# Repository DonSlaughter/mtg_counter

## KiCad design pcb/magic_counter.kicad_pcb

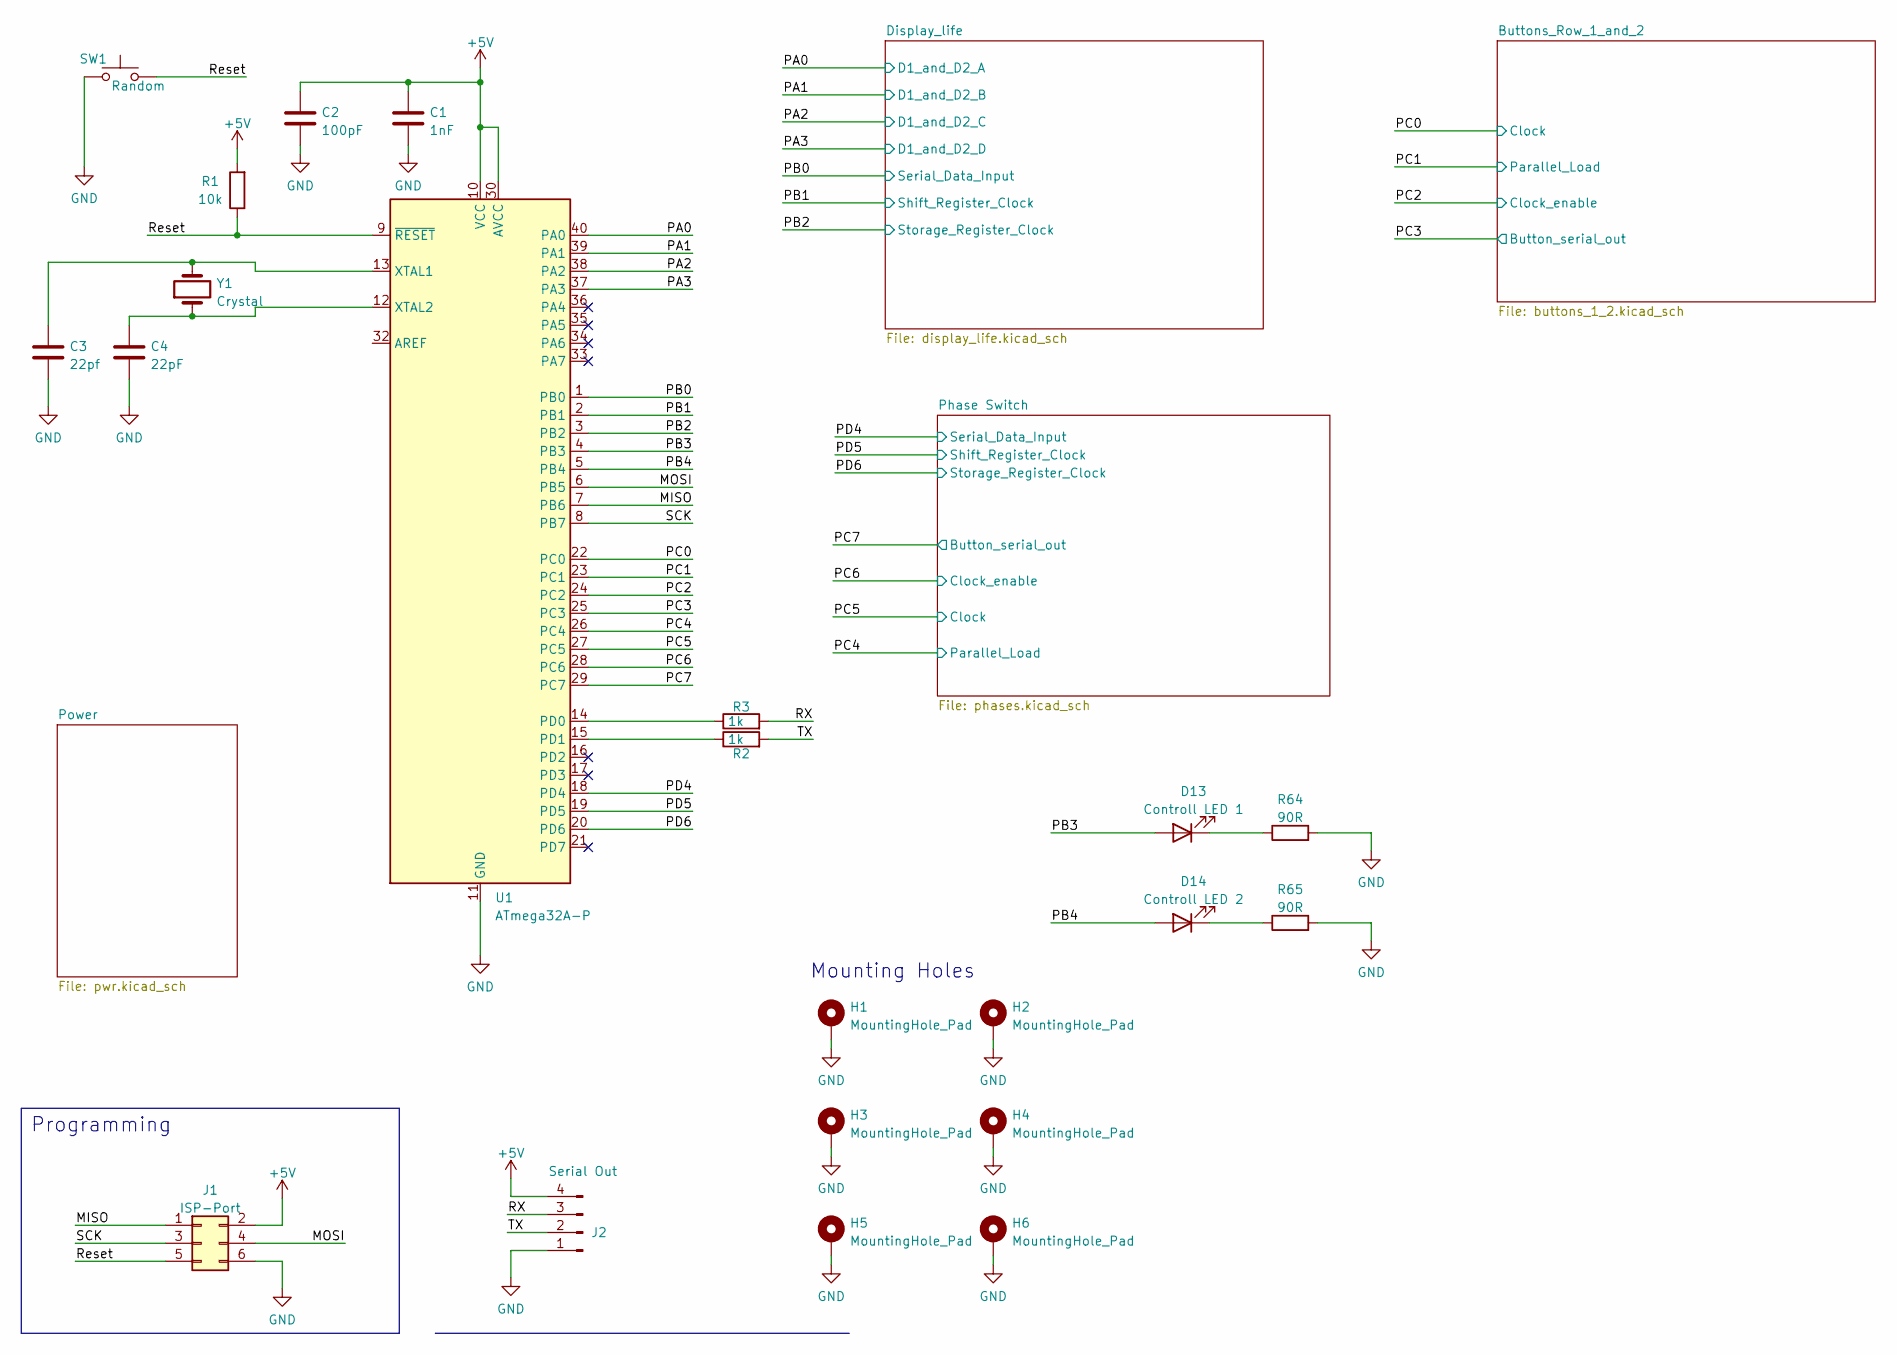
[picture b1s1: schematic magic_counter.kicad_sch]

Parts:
C1: 1nF; C_Disc_D3.8mm_W2.6mm_P2.50mm
C2: 100pF; C_Disc_D3.8mm_W2.6mm_P2.50mm
C3: 22pf; C_Disc_D3.8mm_W2.6mm_P2.50mm
C4: 22pF; C_Disc_D3.8mm_W2.6mm_P2.50mm
D13: Controll LED 1; LED_D5.0mm
D14: Controll LED 2; LED_D5.0mm
H1, H2, H3, H4, H5, H6: MountingHole_Pad; MountingHole_3.2mm_M3_DIN965_Pad
J1: ISP-Port; IDC-Header_2x03_P2.54mm_Vertical
J2: Serial Out; PinHeader_1x04_P2.54mm_Vertical
R1: 10k; R_Axial_DIN0207_L6.3mm_D2.5mm_P7.62mm_Horizontal
R2, R3: 1k; R_Axial_DIN0207_L6.3mm_D2.5mm_P7.62mm_Horizontal
R64, R65: 90R; R_Axial_DIN0207_L6.3mm_D2.5mm_P7.62mm_Horizontal
SW1: Random; SW_PUSH_6mm_H5mm
U1: ATmega32A-P; DIP-40_W15.24mm_LongPads
Y1: Crystal; Crystal_HC49-4H_Vertical

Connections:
+5V: C1.1, C2.1, J1.2, J2.4, R1.2, U1.10 (VCC), U1.30 (AVCC); also elsewhere on the board
/MISO: J1.1, U1.7 (PB6)
/MOSI: J1.4, U1.6 (PB5)
/PA0: U1.40 (PA0); also elsewhere on the board
/PA1: U1.39 (PA1); also elsewhere on the board
/PA2: U1.38 (PA2); also elsewhere on the board
/PA3: U1.37 (PA3); also elsewhere on the board
/PB0: U1.1 (PB0); also elsewhere on the board
/PB1: U1.2 (PB1); also elsewhere on the board
/PB2: U1.3 (PB2); also elsewhere on the board
/PB3: D13.2 (A), U1.4 (PB3)
/PB4: D14.2 (A), U1.5 (PB4)
/PC0: U1.22 (PC0); also elsewhere on the board
/PC1: U1.23 (PC1); also elsewhere on the board
/PC2: U1.24 (PC2); also elsewhere on the board
/PC3: U1.25 (PC3); also elsewhere on the board
/PC4: U1.26 (PC4); also elsewhere on the board
/PC5: U1.27 (PC5); also elsewhere on the board
/PC6: U1.28 (PC6); also elsewhere on the board
/PC7: U1.29 (PC7); also elsewhere on the board
/PD4: U1.18 (PD4); also elsewhere on the board
/PD5: U1.19 (PD5); also elsewhere on the board
/PD6: U1.20 (PD6); also elsewhere on the board
/RX: J2.3, R3.2
/Reset: J1.5, R1.1, SW1.2, U1.9 (~RESET)
/SCK: J1.3, U1.8 (PB7)
/TX: J2.2, R2.2
GND: C1.2, C2.2, C3.2, C4.2, H1.1, H2.1, H3.1, H4.1, H5.1, H6.1, J1.6, J2.1, R64.2, R65.2, SW1.1, U1.11 (GND), U1.31 (GND); also elsewhere on the board
unnamed: C3.1, U1.13 (XTAL1), Y1.2
unnamed: C4.1, U1.12 (XTAL2), Y1.1
unnamed: D13.1 (K), R64.1
unnamed: D14.1 (K), R65.1
unnamed: R2.1, U1.15 (PD1)
unnamed: R3.1, U1.14 (PD0)

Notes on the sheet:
Mounting Holes
Programming

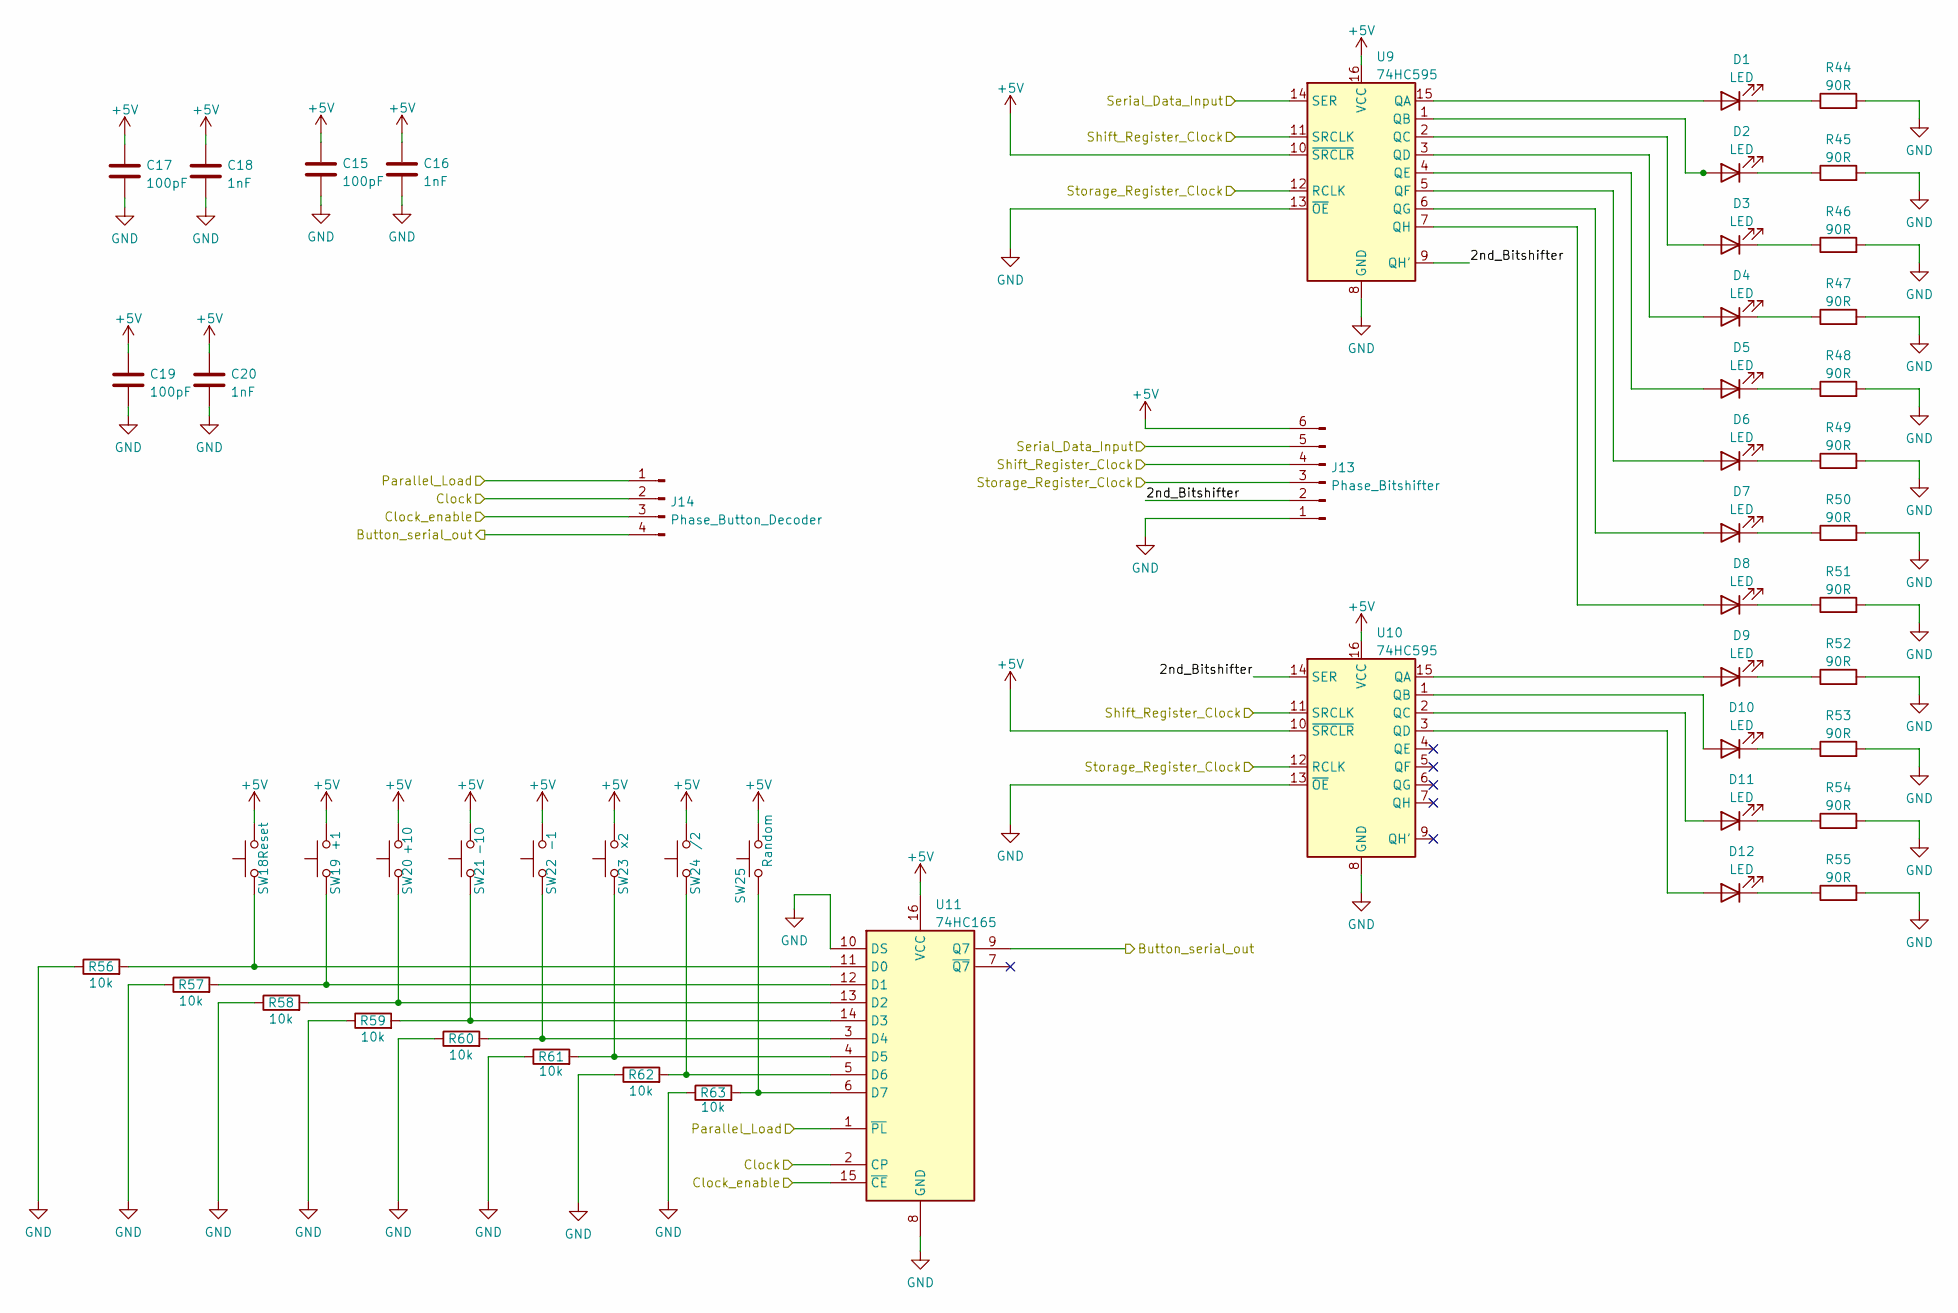
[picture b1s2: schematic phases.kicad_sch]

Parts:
C15, C17, C19: 100pF; C_Disc_D3.8mm_W2.6mm_P2.50mm
C16, C18, C20: 1nF; C_Disc_D3.8mm_W2.6mm_P2.50mm
D1, D2, D3, D4, D5, D6, D7, D8, D9, D10, D11, D12: LED; LED_D5.0mm
J13: Phase_Bitshifter; PinHeader_1x06_P2.54mm_Vertical
J14: Phase_Button_Decoder; PinHeader_1x04_P2.54mm_Vertical
R44, R45, R46, R47, R48, R49, R50, R51, R52, R53, R54, R55: 90R; R_Axial_DIN0207_L6.3mm_D2.5mm_P7.62mm_Horizontal
R56, R57, R58, R59, R60, R61, R62, R63: 10k; R_Axial_DIN0207_L6.3mm_D2.5mm_P7.62mm_Horizontal
SW18: Reset; SW_PUSH_6mm_H5mm
SW19: +1; SW_PUSH_6mm_H5mm
SW20: +10; SW_PUSH_6mm_H5mm
SW21: -10; SW_PUSH_6mm_H5mm
SW22: -1; SW_PUSH_6mm_H5mm
SW23: x2; SW_PUSH_6mm_H5mm
SW24: /2; SW_PUSH_6mm_H5mm
SW25: Random; SW_PUSH_6mm_H5mm
U9, U10: 74HC595; DIP-16_W7.62mm_LongPads
U11: 74HC165; DIP-16_W7.62mm_LongPads

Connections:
+5V: C15.1, C16.1, C17.1, C18.1, C19.1, C20.1, J13.6, SW18.2, SW19.2, SW20.2, SW21.2, SW22.2, SW23.2, SW24.2, SW25.2, U9.10 (~SRCLR), U9.16 (VCC), U10.10 (~SRCLR), U10.16 (VCC), U11.16 (VCC); also elsewhere on the board
/PC4: J14.1, U11.1 (~PL); also elsewhere on the board
/PC5: J14.2, U11.2 (CP); also elsewhere on the board
/PC6: J14.3, U11.15 (~CE); also elsewhere on the board
/PC7: J14.4, U11.9 (Q7); also elsewhere on the board
/PD4: J13.5, U9.14 (SER); also elsewhere on the board
/PD5: J13.4, U9.11 (SRCLK), U10.11 (SRCLK); also elsewhere on the board
/PD6: J13.3, U9.12 (RCLK), U10.12 (RCLK); also elsewhere on the board
/Phase Switch/2nd_Bitshifter: J13.2, U9.9 (QH'), U10.14 (SER)
GND: C15.2, C16.2, C17.2, C18.2, C19.2, C20.2, J13.1, R44.2, R45.2, R46.2, R47.2, R48.2, R49.2, R50.2, R51.2, R52.2, R53.2, R54.2, R55.2, R56.1, R57.1, R58.1, R59.1, R60.1, R61.1, R62.1, R63.1, U9.8 (GND), U9.13 (~OE), U10.8 (GND), U10.13 (~OE), U11.8 (GND), U11.10 (DS); also elsewhere on the board
unnamed: D1.1 (K), R44.1
unnamed: D1.2 (A), U9.15 (QA)
unnamed: D2.1 (K), R45.1
unnamed: D2.2 (A), U9.1 (QB)
unnamed: D3.1 (K), R46.1
unnamed: D3.2 (A), U9.2 (QC)
unnamed: D4.1 (K), R47.1
unnamed: D4.2 (A), U9.3 (QD)
unnamed: D5.1 (K), R48.1
unnamed: D5.2 (A), U9.4 (QE)
unnamed: D6.1 (K), R49.1
unnamed: D6.2 (A), U9.5 (QF)
unnamed: D7.1 (K), R50.1
unnamed: D7.2 (A), U9.6 (QG)
unnamed: D8.1 (K), R51.1
unnamed: D8.2 (A), U9.7 (QH)
unnamed: D9.1 (K), R52.1
unnamed: D9.2 (A), U10.15 (QA)
unnamed: D10.1 (K), R53.1
unnamed: D10.2 (A), U10.1 (QB)
unnamed: D11.1 (K), R54.1
unnamed: D11.2 (A), U10.2 (QC)
unnamed: D12.1 (K), R55.1
unnamed: D12.2 (A), U10.3 (QD)
unnamed: R56.2, SW18.1, U11.11 (D0)
unnamed: R57.2, SW19.1, U11.12 (D1)
unnamed: R58.2, SW20.1, U11.13 (D2)
unnamed: R59.2, SW21.1, U11.14 (D3)
unnamed: R60.2, SW22.1, U11.3 (D4)
unnamed: R61.2, SW23.1, U11.4 (D5)
unnamed: R62.2, SW24.1, U11.5 (D6)
unnamed: R63.2, SW25.1, U11.6 (D7)

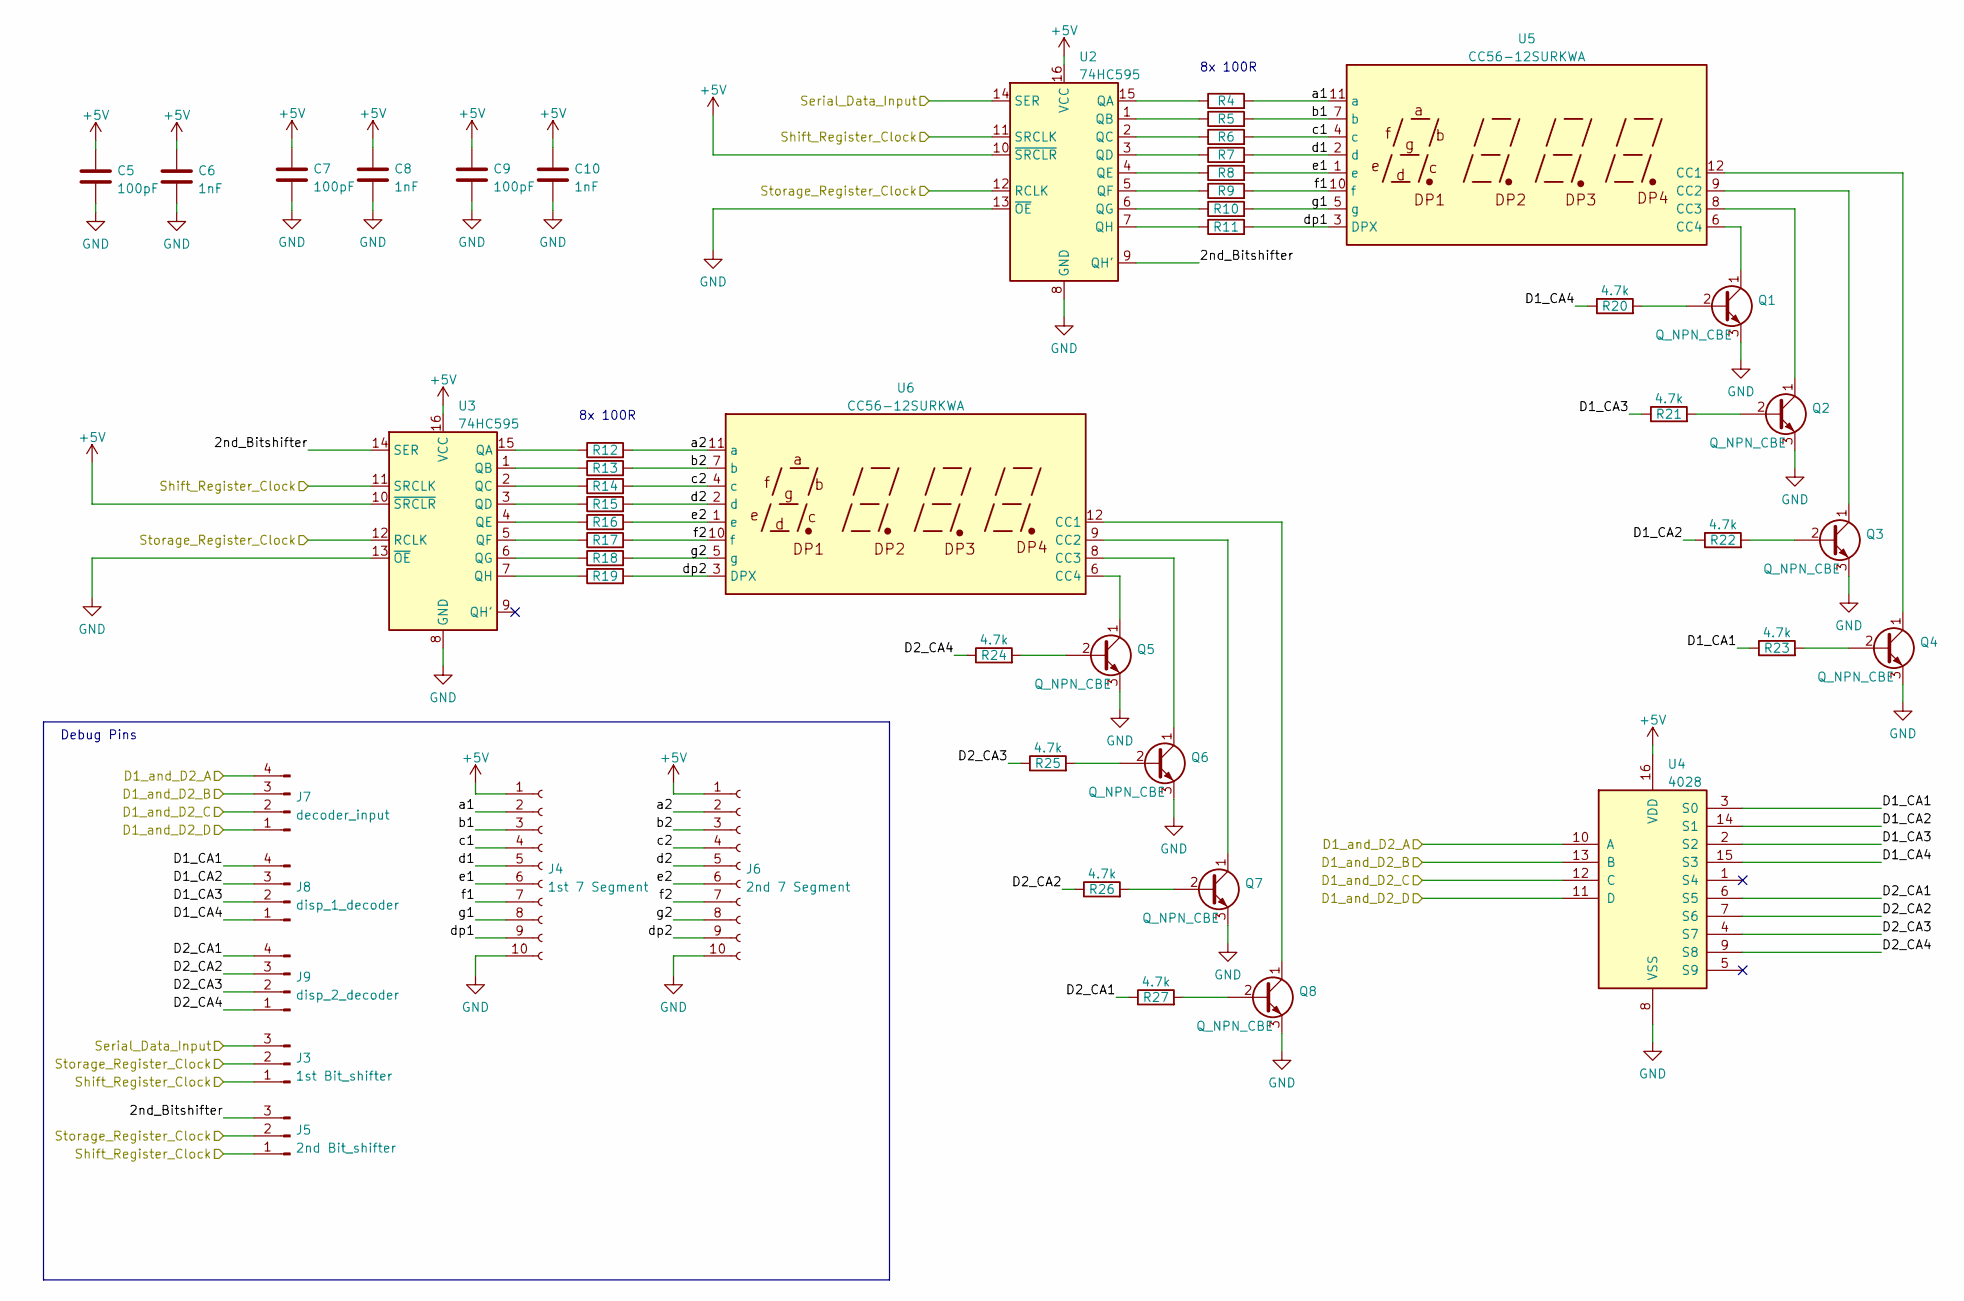
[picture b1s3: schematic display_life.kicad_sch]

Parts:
C5, C7, C9: 100pF; C_Disc_D3.8mm_W2.6mm_P2.50mm
C6, C8, C10: 1nF; C_Disc_D3.8mm_W2.6mm_P2.50mm
J3: 1st Bit_shifter; PinHeader_1x03_P2.54mm_Vertical
J4: 1st 7 Segment; PinHeader_1x10_P2.54mm_Vertical
J5: 2nd Bit_shifter; PinHeader_1x03_P2.54mm_Vertical
J6: 2nd 7 Segment; PinHeader_1x10_P2.54mm_Vertical
J7: decoder_input; PinHeader_1x04_P2.54mm_Vertical
J8: disp_1_decoder; PinHeader_1x04_P2.54mm_Vertical
J9: disp_2_decoder; PinHeader_1x04_P2.54mm_Vertical
Q1, Q2, Q3, Q4, Q5, Q6, Q7, Q8: Q_NPN_CBE; TO-92_Inline_Wide
R4, R5, R6, R7, R8, R9, R10, R11, R12, R13, R14, R15, R16, R17, R18, R19: 100R; R_Axial_DIN0207_L6.3mm_D2.5mm_P7.62mm_Horizontal
R20, R21, R22, R23, R24, R25, R26, R27: 4.7k; R_Axial_DIN0207_L6.3mm_D2.5mm_P7.62mm_Horizontal
U2, U3: 74HC595; DIP-16_W7.62mm_LongPads
U4: 4028; DIP-16_W7.62mm_LongPads
U5, U6: CC56-12SURKWA; CA56-12SURKWA

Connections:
+5V: C5.1, C6.1, C7.1, C8.1, C9.1, C10.1, J4.1, J6.1, U2.10 (~SRCLR), U2.16 (VCC), U3.10 (~SRCLR), U3.16 (VCC), U4.16 (VDD); also elsewhere on the board
/Display_life/2nd_Bitshifter: J5.3, U2.9 (QH'), U3.14 (SER)
/Display_life/D1_CA1: J8.4, R23.1, U4.3 (S0)
/Display_life/D1_CA2: J8.3, R22.1, U4.14 (S1)
/Display_life/D1_CA3: J8.2, R21.1, U4.2 (S2)
/Display_life/D1_CA4: J8.1, R20.1, U4.15 (S3)
/Display_life/D2_CA1: J9.4, R27.1, U4.6 (S5)
/Display_life/D2_CA2: J9.3, R26.1, U4.7 (S6)
/Display_life/D2_CA3: J9.2, R25.1, U4.4 (S7)
/Display_life/D2_CA4: J9.1, R24.1, U4.9 (S8)
/Display_life/a1: J4.2, R4.2, U5.11 (a)
/Display_life/a2: J6.2, R12.2, U6.11 (a)
/Display_life/b1: J4.3, R5.2, U5.7 (b)
/Display_life/b2: J6.3, R13.2, U6.7 (b)
/Display_life/c1: J4.4, R6.2, U5.4 (c)
/Display_life/c2: J6.4, R14.2, U6.4 (c)
/Display_life/d1: J4.5, R7.2, U5.2 (d)
/Display_life/d2: J6.5, R15.2, U6.2 (d)
/Display_life/dp1: J4.9, R11.2, U5.3 (DPX)
/Display_life/dp2: J6.9, R19.2, U6.3 (DPX)
/Display_life/e1: J4.6, R8.2, U5.1 (e)
/Display_life/e2: J6.6, R16.2, U6.1 (e)
/Display_life/f1: J4.7, R9.2, U5.10 (f)
/Display_life/f2: J6.7, R17.2, U6.10 (f)
/Display_life/g1: J4.8, R10.2, U5.5 (g)
/Display_life/g2: J6.8, R18.2, U6.5 (g)
/PA0: J7.4, U4.10 (A); also elsewhere on the board
/PA1: J7.3, U4.13 (B); also elsewhere on the board
/PA2: J7.2, U4.12 (C); also elsewhere on the board
/PA3: J7.1, U4.11 (D); also elsewhere on the board
/PB0: J3.3, U2.14 (SER); also elsewhere on the board
/PB1: J3.1, J5.1, U2.11 (SRCLK), U3.11 (SRCLK); also elsewhere on the board
/PB2: J3.2, J5.2, U2.12 (RCLK), U3.12 (RCLK); also elsewhere on the board
GND: C5.2, C6.2, C7.2, C8.2, C9.2, C10.2, J4.10, J6.10, Q1.3 (E), Q2.3 (E), Q3.3 (E), Q4.3 (E), Q5.3 (E), Q6.3 (E), Q7.3 (E), Q8.3 (E), U2.8 (GND), U2.13 (~OE), U3.8 (GND), U3.13 (~OE), U4.8 (VSS); also elsewhere on the board
unnamed: Q1.1 (C), U5.6 (CC4)
unnamed: Q1.2 (B), R20.2
unnamed: Q2.1 (C), U5.8 (CC3)
unnamed: Q2.2 (B), R21.2
unnamed: Q3.1 (C), U5.9 (CC2)
unnamed: Q3.2 (B), R22.2
unnamed: Q4.1 (C), U5.12 (CC1)
unnamed: Q4.2 (B), R23.2
unnamed: Q5.1 (C), U6.6 (CC4)
unnamed: Q5.2 (B), R24.2
unnamed: Q6.1 (C), U6.8 (CC3)
unnamed: Q6.2 (B), R25.2
unnamed: Q7.1 (C), U6.9 (CC2)
unnamed: Q7.2 (B), R26.2
unnamed: Q8.1 (C), U6.12 (CC1)
unnamed: Q8.2 (B), R27.2
unnamed: R4.1, U2.15 (QA)
unnamed: R5.1, U2.1 (QB)
unnamed: R6.1, U2.2 (QC)
unnamed: R7.1, U2.3 (QD)
unnamed: R8.1, U2.4 (QE)
unnamed: R9.1, U2.5 (QF)
unnamed: R10.1, U2.6 (QG)
unnamed: R11.1, U2.7 (QH)
unnamed: R12.1, U3.15 (QA)
unnamed: R13.1, U3.1 (QB)
unnamed: R14.1, U3.2 (QC)
unnamed: R15.1, U3.3 (QD)
unnamed: R16.1, U3.4 (QE)
unnamed: R17.1, U3.5 (QF)
unnamed: R18.1, U3.6 (QG)
unnamed: R19.1, U3.7 (QH)

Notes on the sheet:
8x 100R
Debug Pins

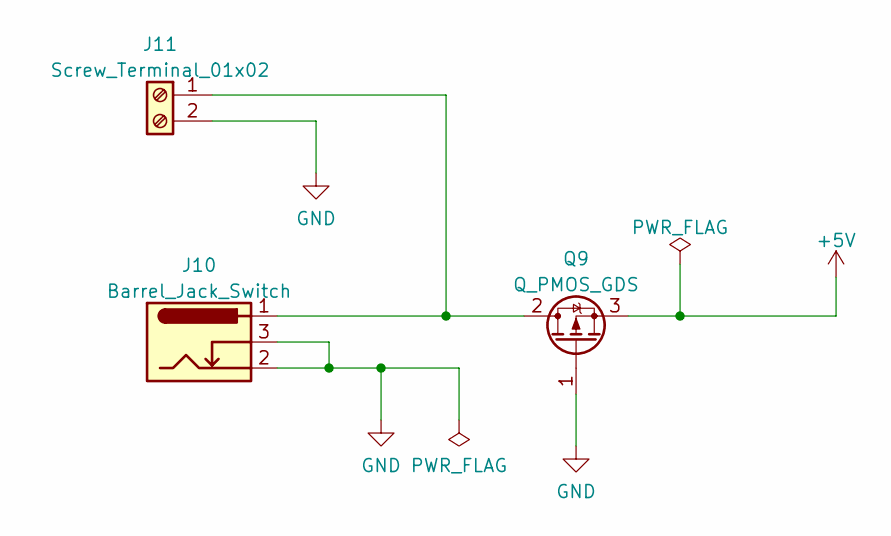
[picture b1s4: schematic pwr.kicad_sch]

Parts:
J10: Barrel_Jack_Switch; BarrelJack_Horizontal
J11: Screw_Terminal_01x02; TerminalBlock_Phoenix_PT-1,5-2-3.5-H_1x02_P3.50mm_Horizontal
Q9: Q_PMOS_GDS; TO-220-3_Horizontal_TabDown

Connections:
+5V: Q9.3 (S); also elsewhere on the board
GND: J10.2, J10.3, J11.2, Q9.1 (G); also elsewhere on the board
unnamed: J10.1, J11.1, Q9.2 (D)

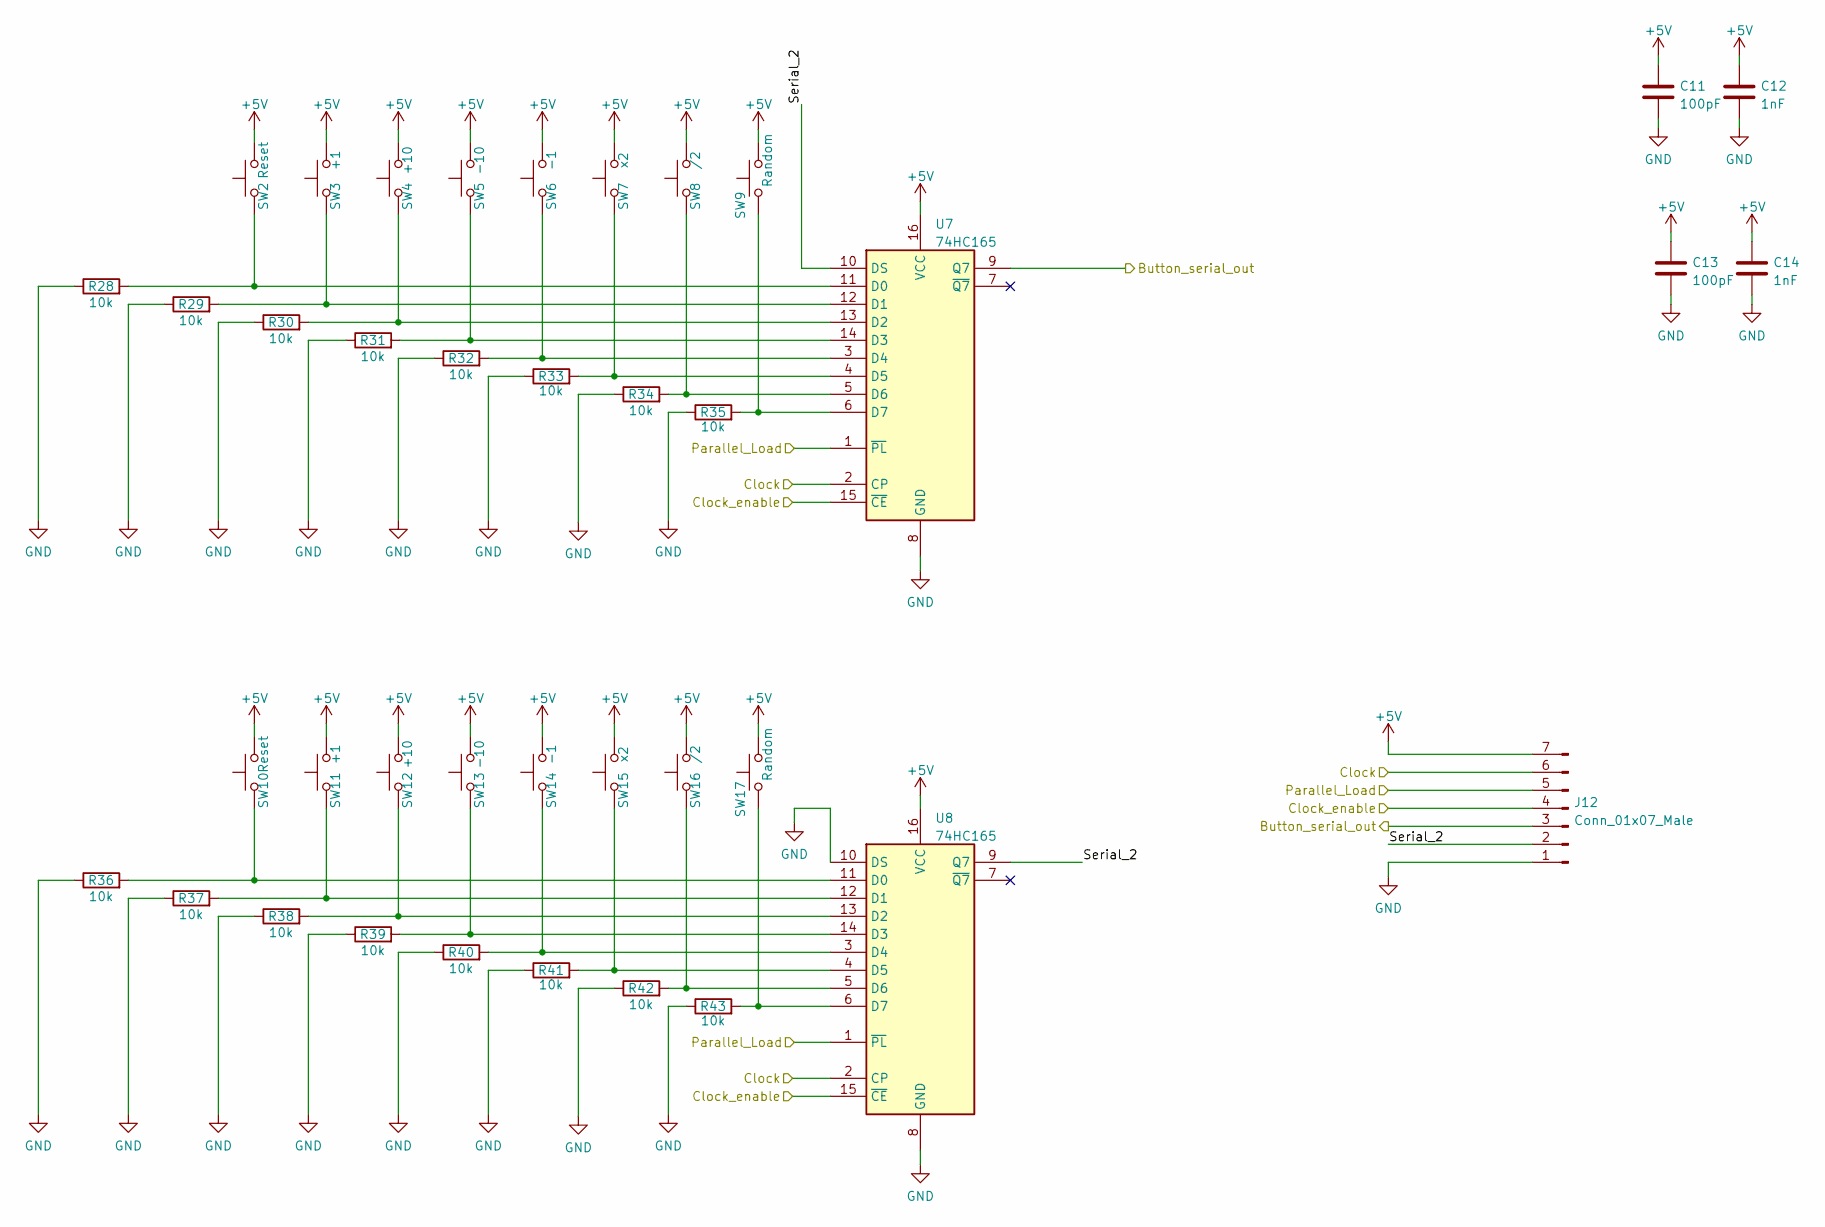
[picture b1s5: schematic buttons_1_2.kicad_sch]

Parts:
C11, C13: 100pF; C_Disc_D3.8mm_W2.6mm_P2.50mm
C12, C14: 1nF; C_Disc_D3.8mm_W2.6mm_P2.50mm
J12: Conn_01x07_Male; PinHeader_1x07_P2.54mm_Vertical
R28, R29, R30, R31, R32, R33, R34, R35, R36, R37, R38, R39, R40, R41, R42, R43: 10k; R_Axial_DIN0207_L6.3mm_D2.5mm_P7.62mm_Horizontal
SW2, SW10: Reset; SW_PUSH_6mm_H5mm
SW3, SW11: +1; SW_PUSH_6mm_H5mm
SW4, SW12: +10; SW_PUSH_6mm_H5mm
SW5, SW13: -10; SW_PUSH_6mm_H5mm
SW6, SW14: -1; SW_PUSH_6mm_H5mm
SW7, SW15: x2; SW_PUSH_6mm_H5mm
SW8, SW16: /2; SW_PUSH_6mm_H5mm
SW9, SW17: Random; SW_PUSH_6mm_H5mm
U7, U8: 74HC165; DIP-16_W7.62mm_LongPads

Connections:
+5V: C11.1, C12.1, C13.1, C14.1, J12.7, SW2.2, SW3.2, SW4.2, SW5.2, SW6.2, SW7.2, SW8.2, SW9.2, SW10.2, SW11.2, SW12.2, SW13.2, SW14.2, SW15.2, SW16.2, SW17.2, U7.16 (VCC), U8.16 (VCC); also elsewhere on the board
/Buttons_Row_1_and_2/Serial_2: J12.2, U7.10 (DS), U8.9 (Q7)
/PC0: J12.6, U7.2 (CP), U8.2 (CP); also elsewhere on the board
/PC1: J12.5, U7.1 (~PL), U8.1 (~PL); also elsewhere on the board
/PC2: J12.4, U7.15 (~CE), U8.15 (~CE); also elsewhere on the board
/PC3: J12.3, U7.9 (Q7); also elsewhere on the board
GND: C11.2, C12.2, C13.2, C14.2, J12.1, R28.1, R29.1, R30.1, R31.1, R32.1, R33.1, R34.1, R35.1, R36.1, R37.1, R38.1, R39.1, R40.1, R41.1, R42.1, R43.1, U7.8 (GND), U8.8 (GND), U8.10 (DS); also elsewhere on the board
unnamed: R28.2, SW2.1, U7.11 (D0)
unnamed: R29.2, SW3.1, U7.12 (D1)
unnamed: R30.2, SW4.1, U7.13 (D2)
unnamed: R31.2, SW5.1, U7.14 (D3)
unnamed: R32.2, SW6.1, U7.3 (D4)
unnamed: R33.2, SW7.1, U7.4 (D5)
unnamed: R34.2, SW8.1, U7.5 (D6)
unnamed: R35.2, SW9.1, U7.6 (D7)
unnamed: R36.2, SW10.1, U8.11 (D0)
unnamed: R37.2, SW11.1, U8.12 (D1)
unnamed: R38.2, SW12.1, U8.13 (D2)
unnamed: R39.2, SW13.1, U8.14 (D3)
unnamed: R40.2, SW14.1, U8.3 (D4)
unnamed: R41.2, SW15.1, U8.4 (D5)
unnamed: R42.2, SW16.1, U8.5 (D6)
unnamed: R43.2, SW17.1, U8.6 (D7)

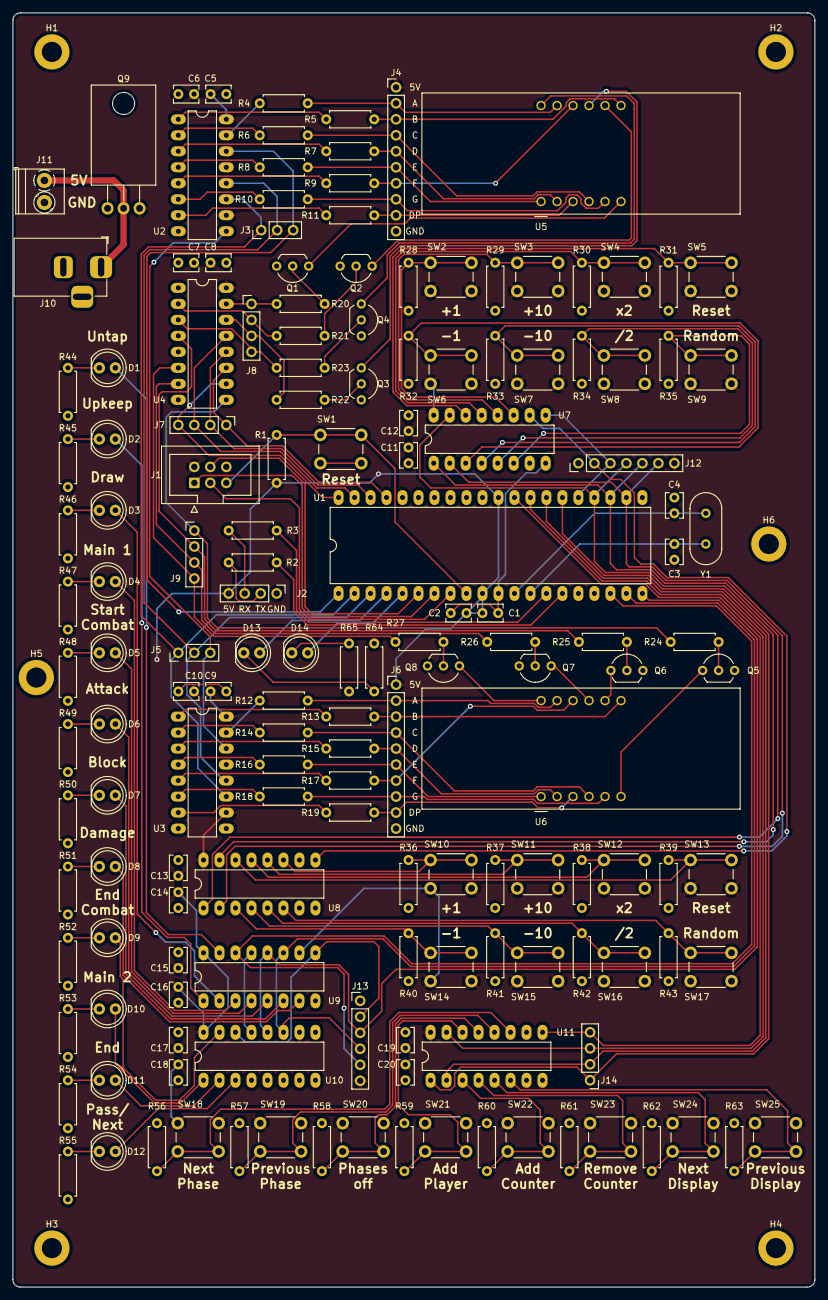
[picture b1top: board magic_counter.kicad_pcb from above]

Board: 2 copper layers, 127.4 x 202.4 mm, 165 parts (0 on the bottom side), 142 nets.

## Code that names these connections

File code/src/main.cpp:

#include <Arduino.h>
#include "led.h"
#include "hc165.h"
#include "hc595.h"
#include "cd4028.h"
#include "pins_arduino.h"

//Pin declarations
//control LED's
const uint8_t led_pin_01 = PIN_PB3;
const uint8_t led_pin_02 = PIN_PB4;

//Phase and Counter Buttons
const uint8_t parallel_load_1 = PIN_PC4;
const uint8_t clock_enable_1 = PIN_PC6;
const uint8_t clock_1 = PIN_PC5;
const uint8_t button_serial_out_1 = PIN_PC7;

//Display Button Rows

//Phase LED HC595 Pins
const uint8_t ser_data_led = PIN_PD4;
const uint8_t shift_reg_led = PIN_PD5;
const uint8_t latch_pin_led = PIN_PD6;

//Display 1 HC595
const uint8_t ser_data_disp = PIN_PB0;
const uint8_t shift_reg_disp = PIN_PB1;
const uint8_t latch_pin_disp = PIN_PB2;

//Dezimal Decoder
const uint8_t dec_encoder_a = PIN_PA0;
const uint8_t dec_encoder_b = PIN_PA1;
const uint8_t dec_encoder_c = PIN_A2;
const uint8_t dec_encoder_d = PIN_A3;

led led_01(led_pin_01);
led led_02(led_pin_02);

//Classes
hc165 bottom_row(parallel_load_1, clock_enable_1, clock_1, button_serial_out_1);
hc595 phases(latch_pin_led, shift_reg_led, ser_data_led);
hc595 displays(latch_pin_disp, shift_reg_disp, ser_data_disp);
cd4028 bcd(dec_encoder_a, dec_encoder_b, dec_encoder_c, dec_encoder_d);

uint8_t input_bottom_row;

void setup()
{
	Serial.begin(9600);
	phases.update_phases(1);
	led_01.on();

}

void loop()
{
	input_bottom_row = bottom_row.read_value();
	switch (input_bottom_row) {
		case 1:
			phases.update_phases(1);
			break;
		case 2:
			phases.update_phases(-1);
			break;
		case 4:
			phases.update_phases(127);
			break;
		default:
			break;
	}
	//Display tests:
		bcd.display(1);
		displays.update_display(8,8);
		bcd.display(5);
		displays.update_display(8,8);
}

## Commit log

2022-06-18 test layout and first traces
2022-06-18 new layout test
2022-06-19 reassigned designators and layout progress
2022-06-20 board besprechung
2022-06-22 new tighter layout
2022-07-01 gitignore added
2022-07-01 Drop files from .gitignore
2022-07-28 datasheets added
2022-07-28 datasheet added
2022-08-02 fewer parts and reduced to prototyping board with more logic analyzer pins
2022-08-03 reduced to 2 displays and logig analyzer output added
2022-08-04 layout nearly finished and first traces
2022-08-07 test 1
2022-08-10 new parts and stuff
2022-08-13 finish layout
2022-08-13 new routes
2022-08-14 layout changes
2022-08-19 moved crystal
2022-08-23 new stuff
2022-08-31 production gerber and new pictures
2022-11-01 new layout with usb
2022-11-04 kicad stuff
2022-11-05 code gitignore added
2022-11-05 code gitignore added1
2022-11-05 code gitignore added2
2022-11-05 code test
2022-11-10 new libs
2022-11-11 wip lib hc595 uint16 to uint8
2022-11-12 working phases led change
2022-11-24 working button read
2022-11-24 working backwards
2022-11-25 removed old code
2022-11-25 first display test
2022-12-01 test devtal
2022-12-07 pulldown to signals
2022-12-28 dont know code stuff
2023-01-06 new gnd plane
